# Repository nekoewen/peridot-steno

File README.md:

# The Peridot
The Peridot is a simple QMK-powered mechanical keyboard for using the Plover open source software for steno. If you’re not familiar, check out [the Open Steno Project](http://www.openstenoproject.org/) for links to the free software, learning resources, and other info to help you get started.

There are a number of hobbyist steno keyboard designs out there, and my goal with the Peridot is to make one that’s easy to build (hence I used basic through-hole components throughout) and open source. How much it will cost will depend a lot on the specifics of the components you choose, but it’ll be vastly cheaper than a professional stenotype. Feel free to make, sell, remix, etc.; this is my attempt to give something back to the Plover community.

## Bill of Materials
- 1x Pro Micro or other compatible microcontroller (Elite-C, BIT-C, KB2040, etc.), with matching USB cable
- 8x M2 standoffs
- 16x M2 screws
- 27x MX or Choc key switches; for steno I recommend switches with lighter springs, such as Choc Pink (25gf), Choc Pro Red (35gf) or Gateron Clear (35gf)
- 21 1u keycaps; flatter keycaps that make it easier to press two keys with one finger are generally better, such as MBK or WRK keycaps for Choc switches or F10 keycaps for MX switches.
- 6x 2u keycaps; particularly for MX switches, stabilizers are recommended but not required
- 4 or more adhesive rubber feet
- 27x 1N4148 through-hole diodes
- 2-pin reset switch (optional; 3x6x2mm DIP-2P switch, the same kind used on the Corne keyboard)
- WS2182 LED strip (optional)

## Tools
- Soldering iron with solder
- Wire clippers
- Wire stripper (if including an LED strip)
- Screwdriver
- Diode bending tool (optional; I use [this one](https://www.thingiverse.com/thing:4332520))

## Build Guide
1. Begin with the diodes. Bend the leads, insert them through the holes (the cathode is marked with a black line and should go on the square pad, so that the line on the diode matches the one printed on the PCB). Solder each diode, then use clippers to remove the excess leads.
2. Take your Pro Micro and flash the firmware (see below). I recommend doing this before soldering it just in case you got a bad board.
3. Solder the Pro Micro and its header pins to the underside of the board, with the Pro Micro’s components facing the board. You may want to use your clippers to trim off the excess part of the headers. If you’re adding a reset switch, put it into the PCB (on the same side as the diodes) and solder its pins.
4. From here you should be able to test the keyboard’s functionality. If you plug it in, it should register as a Peridot keyboard, and you can use tweezers or a similar metal object to make contact on the switch pads to create the equivalent of keystrokes. Remember that some of the switches go sideways, so those ones won't work if you're not hitting the correct pair of contacts. If you use the default keymap you'll need to have Plover running for your computer to do anything with the keystrokes; use the "keyboard" keymap instead if you prefer to test it with regular keystrokes. If any of the keys don’t work, check to make sure you have the diodes soldered and facing the right direction, and also that the Pro Micro’s pins are all soldered in.
5. If you’re including an LED strip for pretty lights, use 3 wires to solder the pads on the PCB to the corresponding ones on the strip. Be sure the DIn lead is going to LED DAT on the board, as they won’t work if you attach it to DOut on the LED strip. If you plug it into your computer now, it should light up!
6. Use screws to secure standoffs to the top plate. It's a bit easier to do before you start in on the switches.
7. Once you’re satisfied that the keyboard actually works, you can begin assembling it in earnest. If you’re using stabilizers, put them in place now. Then put the top plate in place, and start pushing switches in place, though the plate and into the PCB so that each switch’s two leads go through the corresponding holes in the PCB. I like to put switches in the corners, solder them in place, and then fill in the rest of the switches. Once you’ve soldered all of the switches, I recommend testing the keyboard again to be sure that you have in fact soldered all of them. Once that’s done you can go ahead and put the keycaps in place.
8. Put the bottom plate in place, and use the remaining screws to secure it in place.
9. Finally, put some adhesive rubber feet on the bottom. You’re done!

## Firmware
You can find a .hex file of the default Peridot firmware in this repository. If you don’t have any need to customize the layout, you can just download this and flash it to your Pro Micro.
1. Install [QMK Toolbox](https://github.com/qmk/qmk_toolbox) if you haven’t already.
2. Open `peridot_default.hex`.
3. Click the “Auto-Flash” checkbox.
4. Connect the Pro Micro to your computer.
5. Bridge the GND and RST pins with a metal object (or if it’s already soldered in place, press the reset switch).
6. QMK Toolbox should automatically flash the firmware for you!

If you want to customize the firmware:
1. Copy the “peridot” folder from the firmware folder here into the “keyboards” folder of your [QMK installation](https://docs.qmk.fm/#/newbs_getting_started). You can modify the files in this folder as desired.
2. Open a terminal window (for your OS if you’re using macOS or Linux, or [QMK MSYS](https://msys.qmk.fm/) if you’re using Windows).
3. Navigate to the QMK folder (typically `cd qmk_firmware`).
4. Type “`make peridot:default`” (or replace “`default`” with the name of your new keymap) and it should compile.
5. Type "`make peridot:default:flash`" (or replace flash with “`dfu`”) to flash it.

If you're using a KB2040 or similar controller, you'll need to use QMK's [Converters](https://github.com/qmk/qmk_firmware/blob/4020674163fc80914059c4c9c3be5c0ae00bd150/docs/feature_converters.md) feature, so for example compiling and flashing for a KB2040 would go as follows:

`qmk flash -c -kb peridot -km default -e CONVERT_TO=kb2040`

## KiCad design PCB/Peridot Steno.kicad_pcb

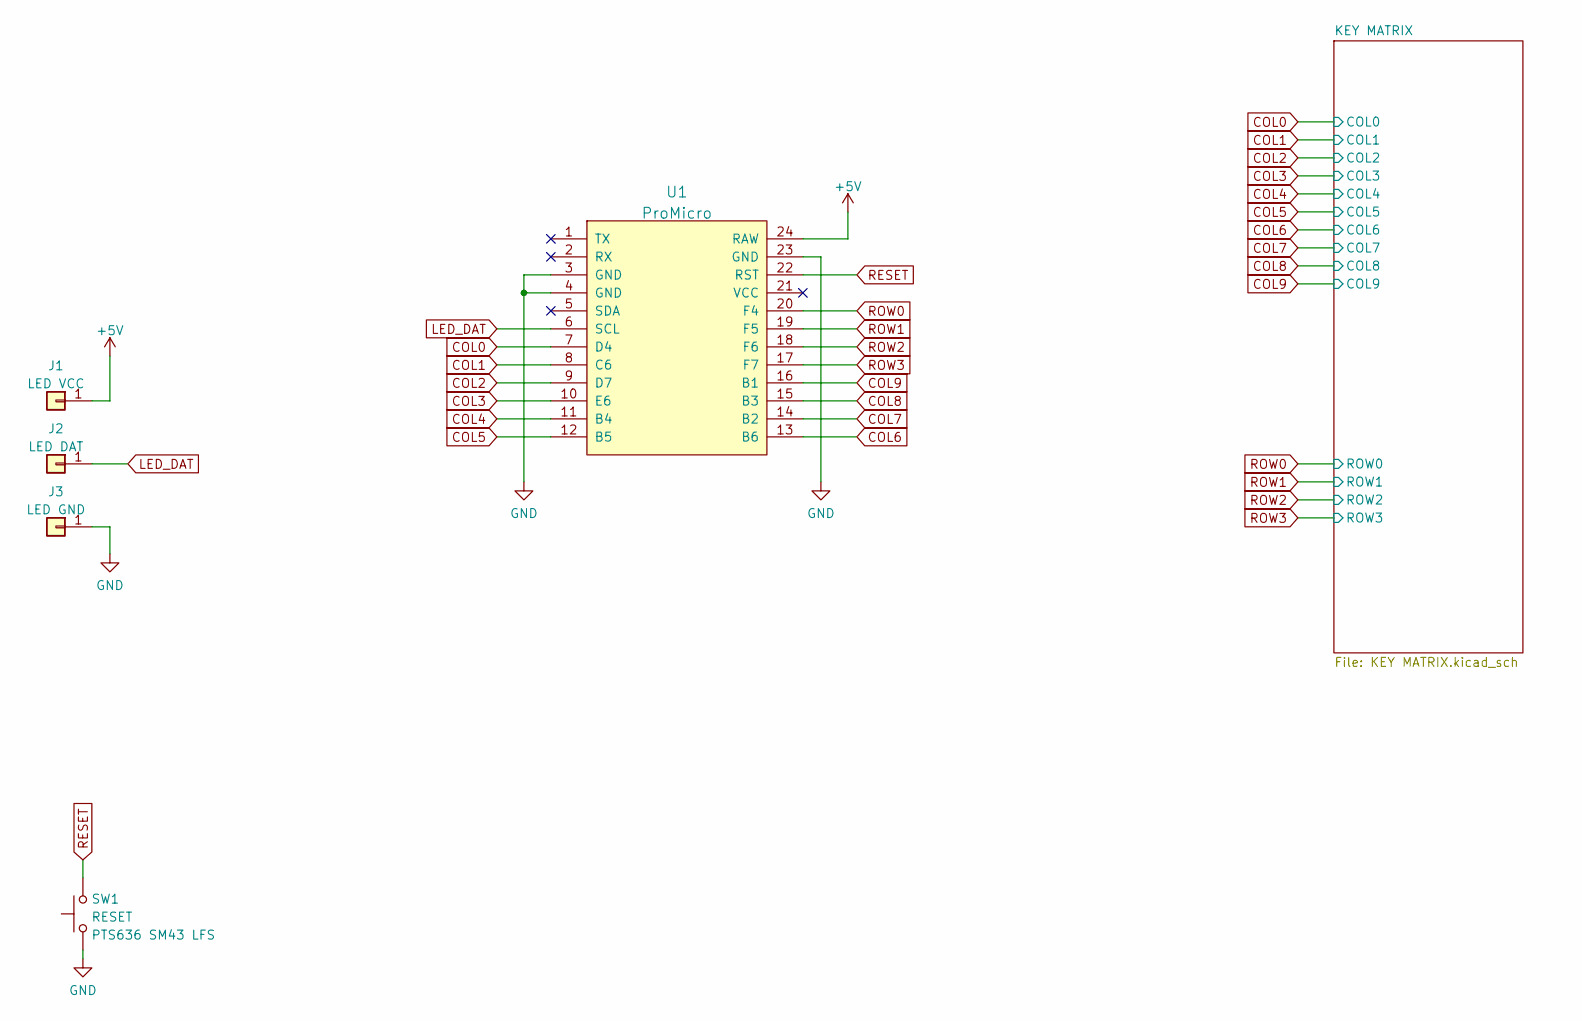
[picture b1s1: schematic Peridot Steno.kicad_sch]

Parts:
J1: LED VCC; TestPoint_THTPad_2.0x2.0mm_Drill1.0mm
J2: LED DAT; TestPoint_THTPad_2.0x2.0mm_Drill1.0mm
J3: LED GND; TestPoint_THTPad_2.0x2.0mm_Drill1.0mm
SW1: RESET; 1825965-1; MPN PTS636 SM43 LFS
U1: ProMicro

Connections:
+5V: J1.1, U1.24 (RAW)
COL0: U1.7 (D4); also elsewhere on the board
COL1: U1.8 (C6); also elsewhere on the board
COL2: U1.9 (D7); also elsewhere on the board
COL3: U1.10 (E6); also elsewhere on the board
COL4: U1.11 (B4); also elsewhere on the board
COL5: U1.12 (B5); also elsewhere on the board
COL6: U1.13 (B6); also elsewhere on the board
COL7: U1.14 (B2); also elsewhere on the board
COL8: U1.15 (B3); also elsewhere on the board
COL9: U1.16 (B1); also elsewhere on the board
GND: J3.1, SW1.1, U1.3 (GND), U1.4 (GND), U1.23 (GND)
LED_DAT: J2.1, U1.6 (SCL)
RESET: SW1.2, U1.22 (RST)
ROW0: U1.20 (F4); also elsewhere on the board
ROW1: U1.19 (F5); also elsewhere on the board
ROW2: U1.18 (F6); also elsewhere on the board
ROW3: U1.17 (F7); also elsewhere on the board

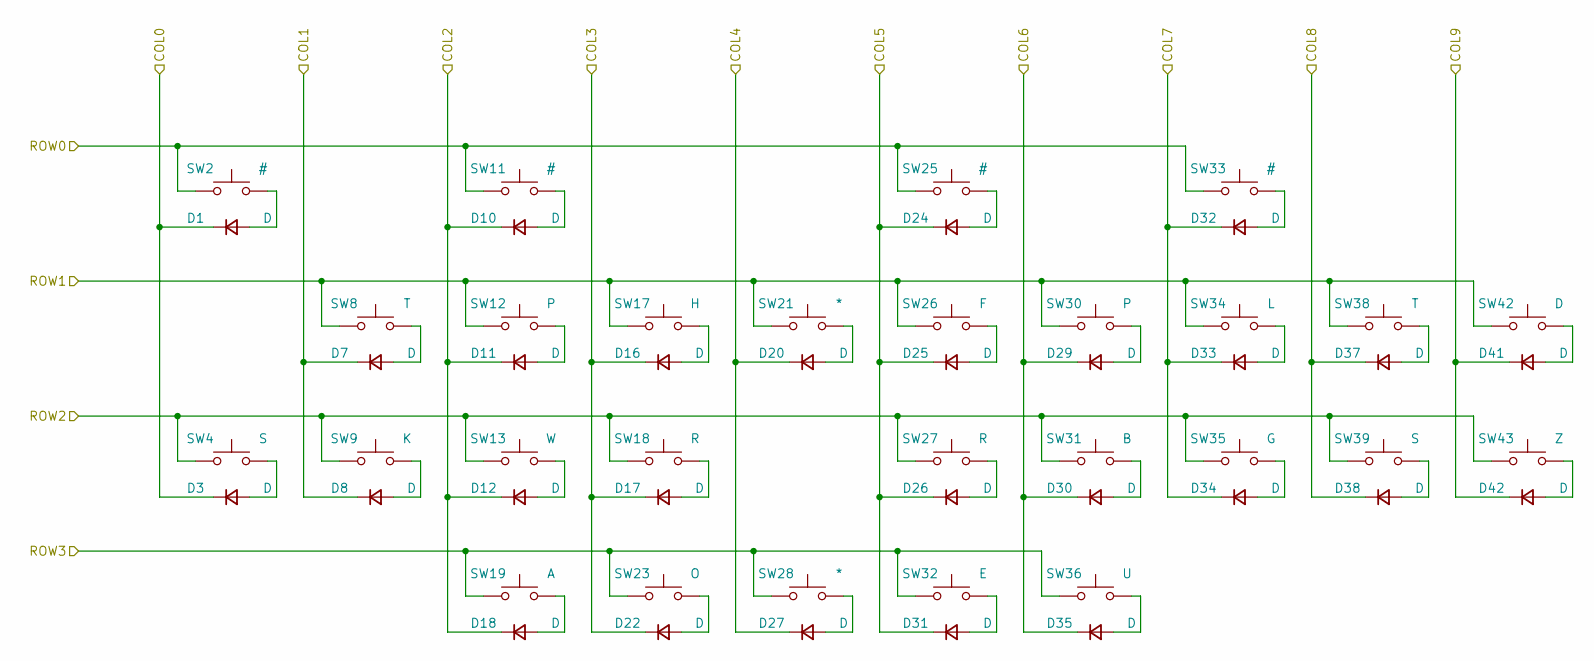
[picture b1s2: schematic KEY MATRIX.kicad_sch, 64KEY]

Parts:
D1, D3, D7, D8, D10, D11, D12, D16, D17, D18, D20, D22, D24, D25, D26, D27, D29, D30, D31, D32, D33, D34, D35, D37, D38, D41, D42: D; D_DO-35_SOD27_P7.62mm_Horizontal
SW2, SW11, SW25, SW33: #; CherryMX_Choc_1u
SW4, SW39: S; CherryMX_Choc_1u
SW8, SW38: T; CherryMX_Choc_1u
SW9: K; CherryMX_Choc_1u
SW12, SW30: P; CherryMX_Choc_1u
SW13: W; CherryMX_Choc_1u
SW17: H; CherryMX_Choc_1u
SW18, SW27: R; CherryMX_Choc_1u
SW19: A; CherryMX_Choc_1u
SW21, SW28: *; CherryMX_Choc_1u
SW23: O; CherryMX_Choc_1u
SW26: F; CherryMX_Choc_1u
SW31: B; CherryMX_Choc_1u
SW32: E; CherryMX_Choc_1u
SW34: L; CherryMX_Choc_1u
SW35: G; CherryMX_Choc_1u
SW36: U; CherryMX_Choc_1u
SW42: D; CherryMX_Choc_1u
SW43: Z; CherryMX_Choc_1u

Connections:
COL0: D1.1 (K), D3.1 (K); also elsewhere on the board
COL1: D7.1 (K), D8.1 (K); also elsewhere on the board
COL2: D10.1 (K), D11.1 (K), D12.1 (K), D18.1 (K); also elsewhere on the board
COL3: D16.1 (K), D17.1 (K), D22.1 (K); also elsewhere on the board
COL4: D20.1 (K), D27.1 (K); also elsewhere on the board
COL5: D24.1 (K), D25.1 (K), D26.1 (K), D31.1 (K); also elsewhere on the board
COL6: D29.1 (K), D30.1 (K), D35.1 (K); also elsewhere on the board
COL7: D32.1 (K), D33.1 (K), D34.1 (K); also elsewhere on the board
COL8: D37.1 (K), D38.1 (K); also elsewhere on the board
COL9: D41.1 (K), D42.1 (K); also elsewhere on the board
unnamed: D1.2 (A), SW2.2
unnamed: D3.2 (A), SW4.2
unnamed: D7.2 (A), SW8.2
unnamed: D8.2 (A), SW9.2
unnamed: D10.2 (A), SW11.2
unnamed: D11.2 (A), SW12.2
unnamed: D12.2 (A), SW13.2
unnamed: D16.2 (A), SW17.2
unnamed: D17.2 (A), SW18.2
unnamed: D18.2 (A), SW19.2
unnamed: D20.2 (A), SW21.2
unnamed: D22.2 (A), SW23.2
unnamed: D24.2 (A), SW25.2
unnamed: D25.2 (A), SW26.2
unnamed: D26.2 (A), SW27.2
unnamed: D27.2 (A), SW28.2
unnamed: D29.2 (A), SW30.2
unnamed: D30.2 (A), SW31.2
unnamed: D31.2 (A), SW32.2
unnamed: D32.2 (A), SW33.2
unnamed: D33.2 (A), SW34.2
unnamed: D34.2 (A), SW35.2
unnamed: D35.2 (A), SW36.2
unnamed: D37.2 (A), SW38.2
unnamed: D38.2 (A), SW39.2
unnamed: D41.2 (A), SW42.2
unnamed: D42.2 (A), SW43.2
ROW0: SW2.1, SW11.1, SW25.1, SW33.1; also elsewhere on the board
ROW1: SW8.1, SW12.1, SW17.1, SW21.1, SW26.1, SW30.1, SW34.1, SW38.1, SW42.1; also elsewhere on the board
ROW2: SW4.1, SW9.1, SW13.1, SW18.1, SW27.1, SW31.1, SW35.1, SW39.1, SW43.1; also elsewhere on the board
ROW3: SW19.1, SW23.1, SW28.1, SW32.1, SW36.1; also elsewhere on the board

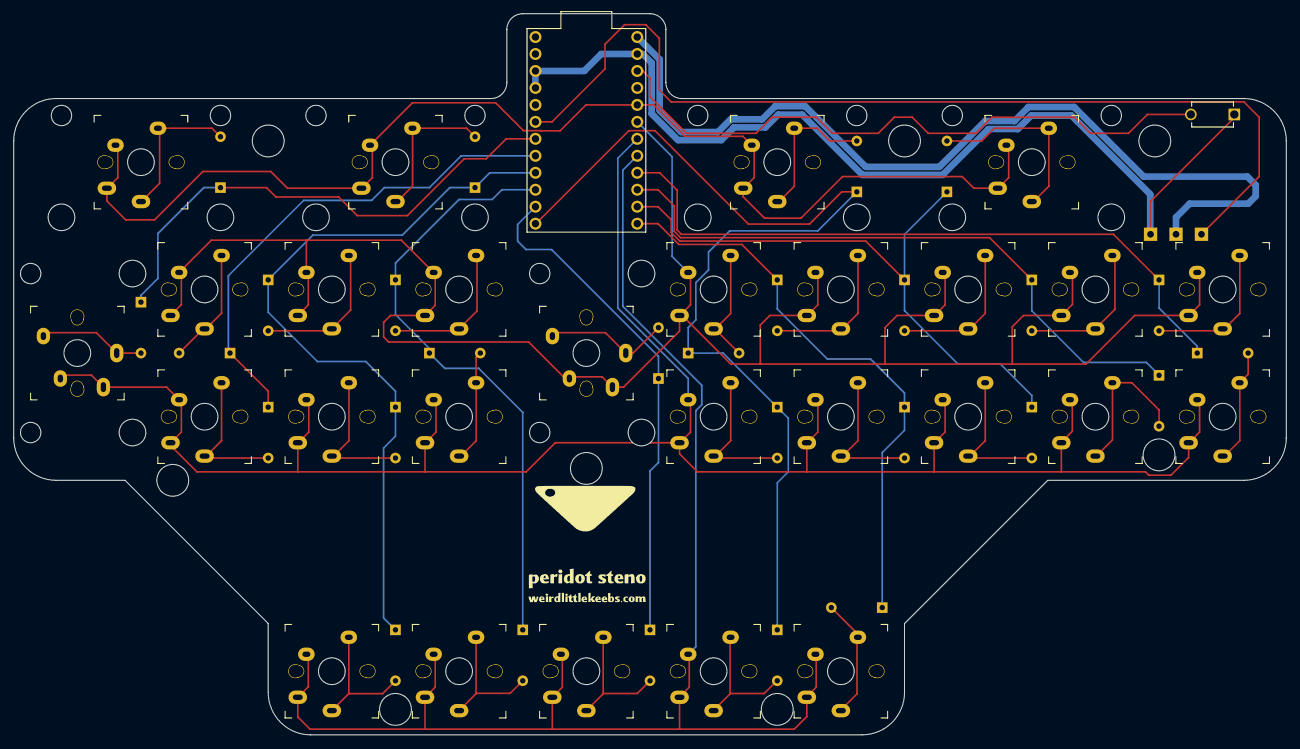
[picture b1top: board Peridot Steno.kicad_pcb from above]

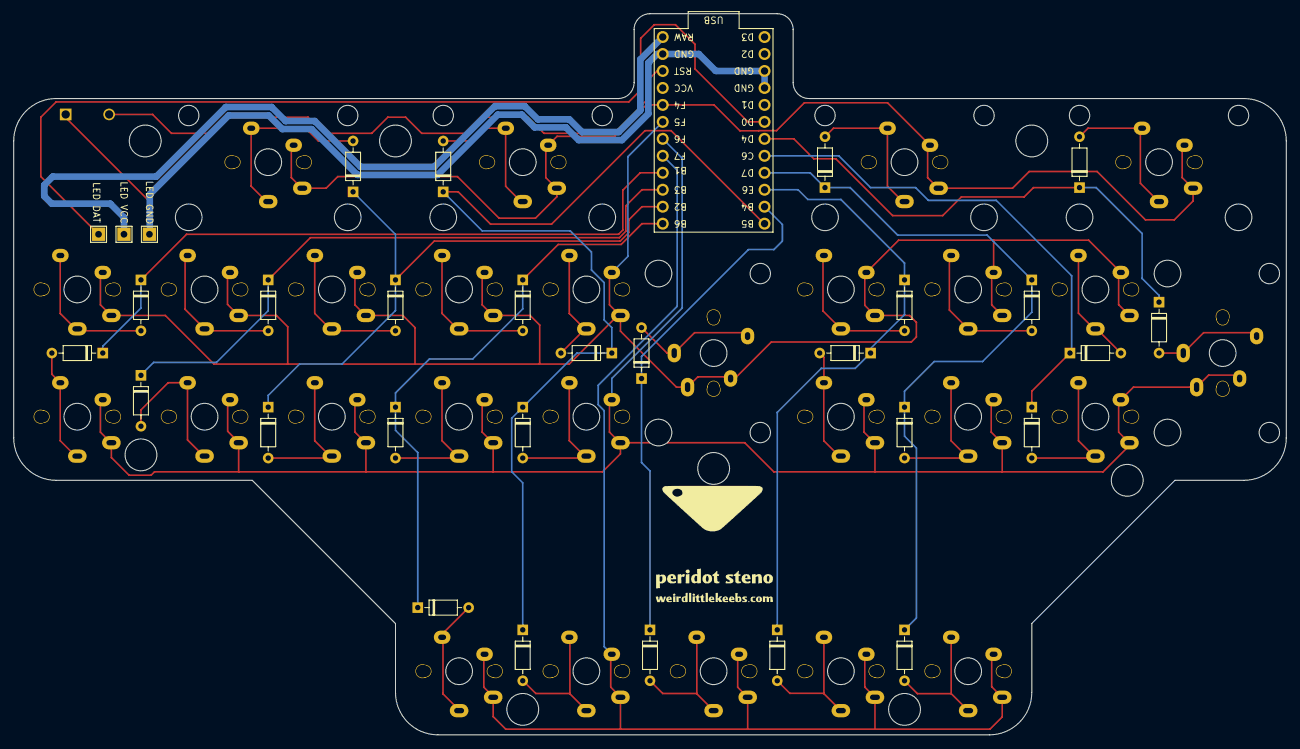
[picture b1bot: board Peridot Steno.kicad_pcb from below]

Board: 2 copper layers, 190.5 x 107.9 mm, 59 parts (30 on the bottom side), 45 nets.

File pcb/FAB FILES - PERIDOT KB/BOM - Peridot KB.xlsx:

Ref | Qnty | Value | Footprint | MPN | MANUFACTURER
D1, D3, D7, D8, D10, D11, D12, D16, D17, D18, D20, D22, D24, D25, D26, D27, D29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 | 27 | D | Diode_THT:D_DO-35_SOD27_P7.62mm_Horizontal | 1N4148 | onsemi
J1, | 1 | LED VCC | TestPoint:TestPoint_THTPad_2.0x2.0mm_Drill1.0mm | DNP | DNP
J2, | 1 | LED DAT | TestPoint:TestPoint_THTPad_2.0x2.0mm_Drill1.0mm | DNP | DNP
J3, | 1 | LED GND | TestPoint:TestPoint_THTPad_2.0x2.0mm_Drill1.0mm | DNP | DNP
SW1, | 1 | RESET | FOOTPRINTS:1825965-1 | 1825965-1 | TE Connectivity
SW2, SW11, SW25, SW33, | 4 | # | FOOTPRINTS:CherryMX_Choc_1u
SW4, SW39, | 2 | S | FOOTPRINTS:CherryMX_Choc_1u
SW8, SW38, | 2 | T | FOOTPRINTS:CherryMX_Choc_1u
SW9, | 1 | K | FOOTPRINTS:CherryMX_Choc_1u
SW12, SW30, | 2 | P | FOOTPRINTS:CherryMX_Choc_1u
SW13, | 1 | W | FOOTPRINTS:CherryMX_Choc_1u
SW17, | 1 | H | FOOTPRINTS:CherryMX_Choc_1u
SW18, SW27, | 2 | R | FOOTPRINTS:CherryMX_Choc_1u
SW19, | 1 | A | FOOTPRINTS:CherryMX_Choc_1u
SW21, SW28, | 2 | * | FOOTPRINTS:CherryMX_Choc_1u
SW23, | 1 | O | FOOTPRINTS:CherryMX_Choc_1u
SW26, | 1 | F | FOOTPRINTS:CherryMX_Choc_1u
SW31, | 1 | B | FOOTPRINTS:CherryMX_Choc_1u
SW32, | 1 | E | FOOTPRINTS:CherryMX_Choc_1u
SW34, | 1 | L | FOOTPRINTS:CherryMX_Choc_1u
SW35, | 1 | G | FOOTPRINTS:CherryMX_Choc_1u
SW36, | 1 | U | FOOTPRINTS:CherryMX_Choc_1u
SW42, | 1 | D | FOOTPRINTS:CherryMX_Choc_1u
SW43, | 1 | Z | FOOTPRINTS:CherryMX_Choc_1u
U1, | 1 | ProMicro | FOOTPRINTS:ProMicro | Pro Micro | Sparkfun

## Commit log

2023-02-22 Create LICENSE
